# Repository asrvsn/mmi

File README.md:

# A stage-top micromanipulator/incubator 

This repository contains the specifications for a combined micromanipulator/incubator stage insert usable for cell/microorganism handling and immobilization for imaging, particularly during multi-day developmental dynamics.

It is fully open source, containing:
* 3D parts suitable for SLA printing: [insert](hardware/insert/parts), [frame](hardware/frame/parts), [capillary mounts](hardware/capillary_mounts/parts), [lid](hardware/lid/parts)
* PCB schematics and board layouts: [main](hardware/frame/main_pcb), [drive](hardware/frame/drive_pcb), [heating](hardware/lid/heating_pcb), [top plate](hardware/lid/plate_pcb)
* A complete [BOM](bom.xlsx)
* Software and firmware for operation: [app](app), [client](client), [firmware](firmware)
* [Assembly](#3d-printing--assembly) and [operating](#usage-and-operation) instructions

The 3D model and an assembled prototype, side by side:

Features of the insert are:
* A temperature (via Peltier) and flicker-free light-controlled enclosure fitting standard well-plates
* Motorized fine-motion XYZ axes (consisting of optical translation stages) for handling, cutting, and more general actuation of specimens via glass capillaries, jogged at commanded speeds down to ~10 um/s (open loop; the slow end is not yet characterised on the unit). A larger-stroke additional X axis consisting of a more traditional stepper leadscrew enables traversal of the entire well-plate width, allowing for:
* Parallelized capture and imaging of N specimens in a statically held row of capillaries, allowing for better control of batch variations.
* A combined syringe/gravity-driven flow control on all capillaries, allowing for transition between traditional displacement (syringe)-driven actuation suitable for capture and gentler pressure-driven immobilization suitable for imaging during development. The latter method is far more robust for multi-day holds and less perturbative during growth and development, where plastic deformations occur.
* Insert geometry fits into existing standard Zeiss "K" frame-style (110x160mm) stage openings as well as larger (130x160mm).
* Insert geometry and mass also enables stacking atop Z-actuated piezo inserts for rapid Z-stack acquisition. This is made possible by the ~1kg total mass of the insert, within typical 1.5-2kg Z-piezo load limits, and a second 130x160mm catch for the piezo stage's larger opening.
* As an insert, micromanipulation occurs as in motions composed with that of the stages, unlike traditional table-top micromanipulators (e.g. those used in electrophysiology). This enables both more natural user operation during manual placement with visual feedback, and also enables multiple captured specimens to be easily imaged using automated sequences (e.g. in ZEN software) without the need for external sync / triggers.
* Precise temperature control is available via a top-mounted (lid) Peltier assembly. This configuration both keeps the full under surface transparent, allowing RL illumination and imaging of the entire well-plate, and prevents Rayleigh-Benard type instability (convection cells) by heating the top rather than the bottom liquid surface. A fast control loop sets the lid surface temperature via on-board NTC's, while a slower loop changes the lid setpoint using readouts of dual medium-immersed temperature probes. The top-mounted heating lid has an imaging slot which retains TL illumination and widefield imaging capability (though not generally at optimal Kohler configuration due to the thickness of the unit) as well as t-PMT. 
* Blue- and red-shifted illumination using tunable-white CCT LED strips.
* Construction from commercially available hardware and 3D printed parts, with no specialized in-house machining or fabrication facilities required.
* Finally: **being an insert, it is designed for rapid setup and teardown in shared-use microscope facilities.** This is a primary benefit over larger built / bespoke setups e.g. with table-mounted micromanipulators or shrouding incubators.

The primary use-case is in time-lapse confocal laser scanning microscopy (CLSM) during growth and development with accurate simulation of diurnal cycles. Many other uses are possible. The use of a z-piezo insert in combination with SNR boosted acquisition methods (e.g. Zeiss Airyscan) enables rapid acquisition of z-stacks, hence this unit is designed to be compatible with this workflow.

Design notes of the current version (v1; v2 coming soon):
* The micromanipulation capability is fully open-loop (with only limit endstops) relying on visual feedback through eyepieces or cameras. Thus automated return sequences are not currently possible. A goal of v2 is to add position feedback. This will be accomplished by using serial-bus servos in v2, also eliminating the separate motor-drive board entirely (left flap seen above moving with the drive unit) and further reducing mass.
* Flow control (syringe- and gravity-driven) are fully manual, supported beside the microscope using unspecified, laboratory-dependent equipment (e.g. via standard hardware attaching to optical breadboards). V2 will motorize both methods of flow control, enabling integration with the other computer-controlled parts (actuation, lighting, and temperature), enabling some degree of experiment automation. Simultaneously, mounting hardware for the off-scope syringe assemblies will be included and further facilitate rapid setup / teardown.
* SLA printing is currently required due to fine details in the design. V2 will transition to an FDM-friendly design, in which parts can be more dimensionally stable depending on the material.
* In v2, the z-height of the unit will be reduced, enabling more optimal microscope condenser placement for widefield acquisition. 
* **Further firmware updates coming soon.**
<!-- * Firmware status: the drive (jogging, limit switches, halts), the lights and the lid run by hand: light levels and lid duty are set from the app's calibration pages or the protocol's `light` and `lid` commands. The lid's temperature control (the cascade above) and incubator programs (diurnal cycles on the Teensy's clock) are specified in [`firmware/api.md`](firmware/api.md) (9.3) and [`firmware/hardware.md`](firmware/hardware.md), but not yet implemented. -->

The complete Fusion 360 file of the assembly is [here](mmi.f3d).

# BOM

The complete bill of materials, including:
* non-3D printed hardware and adhesives
* stepper and servo motors
* experimental apparati
* through-hole / hand-soldered PCB components 

are in [`bom.xlsx`](bom.xlsx). These sheets organize by supplier and contain helper columns to track order status.

# Control system

Three PCBs make up the v1 control system: 
1. A [main board](hardware/frame/main_pcb) built around a Teensy 4.1 (left)
2. An aluminum-core, Peltier-heated [lid board](hardware/lid/heating_pcb) (center) and a [top-plate pcb](hardware/lid/plate_pcb) acting as a passive radiator.
3. A [motor drive board](hardware/frame/drive_pcb) (top) which moves along with the stepper rail and connects via flexible ribbon cable to the main board.

Send all four off to a PCB assembly service; here we include the assets for JLCPCB in each folder, with the order options in its `jlc/ORDER.md`. Order with those options, not the form's defaults: the heating board and the top plate are aluminium-base boards (ordered as default FR-4 they won't spread the heat), the main and drive boards are 4-layer ENIG with epoxy-filled vias, and the main board is assembled on its bottom side. Upon delivery, hand-soldering of several larger components is necessary, detailed in:
<!-- Follow these guides, which also hold each board's checks before first power (on a current-limited bench supply) and the order in which it meets the mechanical build below: -->

* [Main board](hardware/frame/main_pcb/assembly.md)
* [Lid (heating) board](hardware/lid/heating_pcb/assembly.md)
* [Drive board](hardware/frame/drive_pcb/assembly.md)

# Hardware (3D prints)

# 3D printing & assembly

In the following, we give 3D printing and assembly steps in brief. Detailed print settings are in [hardware/print.md](hardware/print.md).

## Stage insert

Print the [insert file](hardware/insert/parts/insert.step).

Epoxy the 8mm 440C balls to their pockets in `insert` to create a kinematic coupling.

## Unit frame

Print the [unit frame's parts](hardware/frame/parts): one of each, except three each of the two gears and the main enclosure's switch cap ([print.md](hardware/print.md)).

Epoxy magnets and dowels to the underside of `frame` to complete the kinematic coupling: one 8 x 3 mm magnet per pocket, then its dowel pair.

Epoxy balls topside (six: the capillary mount's and lid's couplings). Take the NEMA11 150mm actuator apart: keep the motor with its leadscrew, the carriage on its MGN9 rail, and the leadscrew's end bearing (in the kit's aluminium back plate); the kit's own frame and both aluminium plates aren't used. Press the end bearing into the frame's Ø13.15 seat at the bearing end, flush with the end face. Lay the rail in the frame's groove and bolt it through its 3rd, 5th and 7th holes with 3 x M3x12 socket heads into M3 nuts inset in the frame, tightened in turns to ~0.5 N·m (the nuts sit in resin).

Bolt the motor (3 x M2.5x8 button heads + washers, from inside the frame), snug only, threading the leadscrew through the carriage's nut into the end bearing (any stepper tester spins it quickly; or turn the shaft by hand). Run the carriage to the motor end, so the nut pulls the motor onto the screw's line on its pilot, then tighten the three screws in turns. Test full travel: the effort should stay even. If it tightens toward the motor end, repeat that alignment; toward the bearing end, open the Ø13.15 seat slightly on the side the screw pushes toward and fix the bearing with a drop of epoxy. Finish with a thin film of grease on the screw. Strong print warping or dimensional inaccuracies can make this unavoidable, in which case one option is to not place the end bearing, allowing the screw to move loosely.

Epoxy the 30T gear to the translator knob and bolt the 16T gear to the servo spline (M2.5x8 button head), x3. Translators are compact manual linear stages with a knob drive (not a micrometer head); servos are micro digital servos with a bottom wire exit, used as plain gearmotors. At this step, therefore, remove the servos' control boards (and positioning potentiometers), solder a twisted pair of 26 AWG silicone (~200 mm) to each motor's terminals and bring it out through the same exit ([drive board guide](hardware/frame/drive_pcb/assembly.md), step 8).

Bolt `y_brace` to the Y stage base: 2 x M2x6 button heads through the base into M2 nuts inset in the brace. The table covers the holes, so run the translator back and forth (turn the knob) to reach each of the two inset M2s in turn.

From the top, 2 x M4x8 countersunk through the brace into the base. Epoxy the brace's half of the wrist coupling: a pair of 6 x 2 mm magnets per pocket, then its dowel pair.

Fit the subminiature hinge-lever microswitches (8 per unit, low operating force) to the three printed faces and wire each stage-end pair NC in series with 30 AWG wire (the arm's channel has no room for 26 AWG on all sixteen switch wires): a bridge between the NC pins, a lead from each outer pin. `x_face` takes X's pair and the rail MAX switch (J8, the bearing end), `x_brace` Z's pair, `z_brace` Y's pair and the rail MIN switch (J7, the motor end). Every switch is wired COM to NC, its NO pin cut short ([drive board guide](hardware/frame/drive_pcb/assembly.md), step 9).

Slide the Y servo into `z_brace` (tabs on the wall; 2 x M2x16 into nuts in the side slots), then bolt `z_brace` to the Y table from below: 3 x M4x10 and 2 x M2x10 countersunk.

Bolt the Z stage base to `z_brace` as for Y: 2 x M2x6 button heads into inset M2 nuts, the stage driven to its top end to reach the hole.

Z servo into `x_brace` (2 x M2x16 + nuts), then `x_brace` onto the Z table: 3 x M4x10, 2 x M2x10 countersunk.

X stage base onto `x_brace`: 2 x M2x6 button heads into inset M2 nuts.

X servo into `x_face`, body first (2 x M2x16 + nuts). Bolt the drive board's arm to `x_face`: 2 x M2x20 into nuts recessed in the arm.

`x_face` onto the X table: 3 x M4x10, 3 x M2x10 countersunk, heads on the face.

Drive board, wires first and covers last ([drive board guide](hardware/frame/drive_pcb/assembly.md), steps 3-15):
1. The ribbon: measure the 20-way IDC ribbon (2.54 mm pitch, sockets on both ends) in place (the guide's step 3 dry-fits the tray, the main board and `x_face` for it), as a U-loop from the main board's J1 that rolls with the carriage, and cut the far socket off where it meets J2's pads (~250-300 mm). Solder that end to the J2 pads, red stripe on pad 1, and buzz it (H1) before any switch is wired. Strain relief: a bead of neutral-cure RTV or epoxy across the ribbon (no room for a cable tie).
2. The board into the arm's frame. Per axis, route the servo's motor pair and the switch pair along the arm's channel, cut them to length and solder them: motors to J4-J6, the stop chains to J9/J11/J13, the rail's MIN and MAX switches to J7 and J8. Check them at the IDC socket (H3).
3. Then the housing: back plate + front cover, 4 x M2x10 + nuts.

Slide the rail carriage into `x_face` from the side as shown (its lip hugs the carriage) and bolt the plate to it: 4 x M3x10 countersunk from the top.

Cut two 100 mm lengths of tunable-white 24 V LED strip (COB; cut only at its 50 mm marks, and the walls take up to 120 mm) and stick them on edge to the frame's long inner walls, LEDs facing the plate. Link the strips' 24V, W- and C- pads at the bearing end, and run three leads from the motor end through the frame's lead tunnel to a 3-pin PH plug for the main board's J16 (halved pre-crimped leads: pin 1 24V, pin 2 W- (warm), pin 3 C- (cool); [main board guide](hardware/frame/main_pcb/assembly.md), step 19).

Bolt the main enclosure's tray to the frame's three end pads: 3 x M3x8 countersunk from the frame side into M3 nuts in the tray's bosses.

Main board, hand-assembled and checked through M8 of [its guide](hardware/frame/main_pcb/assembly.md) (Teensy 4.1 in its sockets), into the tray: plug in the rail motor (J3) and the LED strip (J16), the unit off. The rail motor's lead ends in bare wires: make its 4-pin ZH plug as in the guide's step 18 (pin 1 black, 2 green, 3 red, 4 blue), and never plug or unplug it live. Cover on with 3 x M2x20 socket heads into M2 nuts in the tray's back face; switch caps in from the top. The ribbon's IDC socket mates on J1 through the cover's opening.

<!-- The unit's first power-up, everything plugged in, is the main board guide's S1-S3: on the current-limited bench supply first, then the 24 V supply. -->

## Capillary mounts

Print the [capillary mount files](hardware/capillary_mounts/parts).

Epoxy the mount's half of its coupling to its underside: a pair of 8 x 3 mm magnets per pocket, then its dowel pair; glue in the three M2 nuts for the face plate. On `end_effector_base`, epoxy its three Ø6 mm balls (440C or chrome steel: they sit on magnets) and press in the two M2 nuts for the clamp cover from below.

Press 2 mm solid silicone cord (~0.22 m per unit) into the clamping plates' grooves, cut flush: four lengths in `face_plate`, two in `end_effector_clamp`. If using the 3 mm foam cord instead, check the cord parameters in Fusion before printing the plates.

## Peltier-heated lid

Print the [lid frame](hardware/lid/parts/lid_frame.step).

Epoxy the lid frame's half of its coupling: one 8 x 3 mm magnet per pocket, then its dowel pair.

The heating board follows [its guide](hardware/lid/heating_pcb/assembly.md). All its hot-plate work comes before the frame, whose resin softens from ~77 °C:
1. In one hot-plate session (~100 °C):
   * the six 20 x 20 mm Peltier modules on thermal paste, their leads soldered to PE1-PE6;
   * the two medium probes (10k NTC in a Ø3 x 12 mm stainless cap, AWG28 PTFE leads) on J2 and J3, either lead on either pad. Cut the leads to ~55 mm (J2) and ~115 mm (J3) from the cap (46-48 and 107-109 mm in the model, plus leeway), strip ~2 mm and tin;
   * the 7 x 26 AWG lid cable on J1 (twisted in pairs: +24 V/GND, SDA/SCL, IN1/IN2, plus a second GND).
2. Thread the cable through `lid_frame`'s +X tower channel (the frame hangs on it until glued), make its 7-pin PH plug for the main board's J20 (wire n to pin n), and run the board's checks on the main board.
3. Paint the aluminium (chamber) side matt black, put a 7 mm piece of polyimide tape over MH1, MH2, MH4 and MH6, then epoxy the board into `lid_frame`.
4. Conformal coat the copper side with TCO1 (the Peltier string's thermal cutoff) masked, as the coat can glue its contacts shut; mask the Peltier tops and the six screw holes too.
5. Dress the probe leads: each pair runs from its pads over the imaging slot's edge, down through the slot and along the board's underside, then down to its cap, which lies flat on the dish floor just past the coverslips' outer end, tip away from you: J2's through the slot's -X end, J3's between R16 and PE2 to the slot's +Y edge, then under the board to the +X end.

Top plate on thermal paste over the six Peltiers, 6 x M3x10 button heads from below into M3 nuts on top: tighten evenly, the Peltiers sandwiched tight between board and plate. Then line the slot with polyimide tape, bridging the gap between board and plate, and run a bead of neutral-cure silicone into the tower's channel round the cable (guide steps 15-16).

## Completed unit

# Software

The Teensy 4.1's firmware, a Python client library with a test server that stands in for the unit, and the operator's app.

| | |
|---|---|
| `firmware/` | the firmware (`stage/`), its protocol (`api.md`), parameters, hardware rules and host tests: `firmware/README.md` |
| `client/` | `mmi_client`: the client library (standard library only) and the test server: `client/README.md` |
| `app/` | `mmi_app`: the operator's window, driven by a hand controller or the keyboard: `app/README.md` |
| `env.yml` | the `mmi` conda env: both packages and all they need |
| `start_application` | starts the app, on the unit or a test server (a Mac or Linux) |
| `write_firmware` | builds the firmware, writes it to the Teensy over USB, and checks it (a Mac or Linux) |

## Install

With conda (Miniforge), from this folder:

```sh
conda env create -f env.yml     # once: Python 3.12, PyQt6, pyqtgraph, pygame ..., and client/ + app/ installed editable
conda activate mmi              # for the test server and the tests (start_application finds the env itself)
conda env update -f env.yml     # after env.yml changes
```

Any other Python 3.11+: `pip install -e client -e app` (their `pyproject.toml` list what they need;
`pip install -e "client[test]" -e "app[test]"` adds pytest). The tests: `pytest` in `client/` and in `app/`
(offscreen); the firmware's, `firmware/test/run.sh`.

## Write the firmware

The first flash is part of the main board's bring-up (its guide, step T). For updates: with Teensy USB exposed without enclosure and all board switches off, connect micro-usb to controller PC and execute `./write_firmware`. It builds, uploads, and checks
the `!hello` (`firmware/README.md`, "Building and flashing"). Then, close the enclosure; do not connect to USB during normal operation with 24v plugged in.

## Start the app

```sh
./start_application                  # the unit, over wired Ethernet
./start_application 127.0.0.1        # the test server on this computer (below)
```

- **The unit:** the cable from this computer's Ethernet port or adapter into the unit's J19, the unit on (PWR, SW9). It
waits for the link, gives the interface 192.168.50.1/24 if it hasn't an address there (your password; temporary),
waits for the unit, says which gamepad the app will take, and starts the app.
- **Any other address** skips the Ethernet set-up and waits until something answers there.
- **The app's own arguments** pass through: `--fullscreen`, `-v` (log connects, drops and inputs), `--config my.toml`
(`app/config.example.toml`). It won't start a second app while one is open.
- **Driving:** MOTORS (SW11) on, then the sticks and triggers, and MOTORS off again when done; B (Circle, Space) halts; HOME (PS, Esc) opens the menu:
`app/README.md`, "Controls".

## Test with the test server

```sh
python -m mmi_client.test_server     # shell 1, in the mmi env: the unit on 127.0.0.1:5000, printing what it's sent
./start_application 127.0.0.1        # shell 2: the app, driving it
```

- **It simulates the unit at the protocol level:** the drive with its lease and halt, the stage's travel and its limit
switches, stalls, MOTORS, the lights and the lid (with its thermal model). Options: `--motors-off`, `--strict`,
`0.0.0.0:5000` to be reachable from another machine (the Pi): `client/README.md`.
- **With Fusion 360:** start Fusion with its MCP add-in (it listens on 127.0.0.1:27182) and open the `mmi` design,
with its "kin: rail / X / Z / Y" joints. The test server finds it by itself and drives those joints, so every jog
moves the model on screen, stopping at the stage's ends; Ctrl-C puts them back to the as-built pose. Without Fusion
it simply runs; `--no-fusion` keeps it out even with Fusion open.

# Experiment preparation

Fluids preparation for an experiment.

## Syringe assembly

Fill the syringe (2.5 mL gastight glass) fully and purge it tip up, to a droplet at the Luer tip. Assemble: the reservoir line's (1/16" ID) female fitting on the stopcock's (3-way female x female x male, locking Luer) male port, the outlet's male fitting in its in-line female port, the syringe into the side port, OFF toward the outlet. The Luer tip is a slip fit, so seat it firmly.

OFF right (toward the reservoir line); push 1 cm to fill the outlet to a droplet.

OFF left; push 1 cm to fill the reservoir line to a droplet at its end.

Line into the reservoir flask (T25 culture flask used as reservoir), its end 1 cm off the floor; pull the plunger fully out to refill. Repeat per syringe assembly.

## Capillaries

We generally use 2.00 mm OD x 1.00 mm ID borosilicate capillaries. Leave blunt for **dispensing** lines, pull to desired ID for **capture** and **actuation** lines. Follow standard procedures for pulling larger (50-100um) tips as needed, e.g. pulling smaller and then scoring and breaking against ceramic tile. A starting point on a Sutter P-97 with a box filament (from the Sutter Pipette Cookbook's large-tip programs, untested on this glass): run a ramp test, then HEAT = ramp + 25, PULL 0, VEL 140, TIME 100, pressure 200; 2 mm glass should pull 15-25 s after pressing PULL (adjust HEAT in steps of 5). The ID/OD ratio stays about 0.5, so for a 100 um ID tip, score where the OD is about 200 um.

OFF right. Push 10 cm of tubing onto the outlet barb and a blunt (unpulled) capillary 3 mm into its end; push 1 cm to fill to a droplet. Repeat per dispensing capillary.

Dip the dispensor's tip in the sample (e.g. a 60 mm dish) and pull 2 cm back to draw it up the capillary and into the tube.

As for the dispensors, with pulled capture capillaries, tips broken back to ~50 um ID. Repeat per capture capillary.

The same for the two shorter actuator capillaries.

Lay the actuator capillaries in the end effector's grooves and caliper each tip to 20.3 mm beyond the base's end face (the nominal pose, open loop). Clamp cover on: 2 x M2x8 countersunk hex. Keep the capillary tips upright throughout, so no air gets in.

Lay the capillaries on the mount's ramp, the dispensors innermost in each group (8th and 9th): captures to 42.4 mm beyond the mount's end face, dispensors to 39.6 mm. Face plate on: 3 x M2x8. Keep the capillary tips upright throughout, so no air gets in.

## Well plate

Cut two 44 x 16 mm windows in the single-well plate's floor (a rotary tool) for 22 x 50 mm (No. 1.5) coverslips: centred across the plate's width, either side of a 7 mm rib on its centre line, 16.4-60.4 and 67.4-111.4 mm along its length from either outer end. Each coverslip overlaps its window by 3 mm all round, and the row's capillary tips sit over them. File the edges, and clean all surfaces with IPA. Glue the coverslips on using a UV-cured optical adhesive rated USP Class VI, e.g. NOA 81. Rinse with clean solvent (e.g. DI water) and test for leaks. Ensure the coverslips mount from the bottom, as this ensures objectives don't snag on well plate surfaces.

## On the microscope

Insert into microscope's stage insert (standard "K" frame or larger z-piezo openings both supported); well plate in, with ~5 mm of medium (~49 mL).

Lower the frame onto the insert's kinematic coupling.

Snap the end effector onto its wrist coupling and press its two tubes into `x_face`'s clips: the lip clip, then up the vertical clips. Their line runs to the actuators' syringe assembly beside the scope.

Snap the capillary mount onto its coupling; its tubes run to the dispensors' and captures' syringe assemblies.

Lid onto its coupling; its cable into the main board's J20.

Lower the condenser; microscope is ready to image.

# Run experiment

The unit takes 24 V DC, centre positive, into J15 (a 5.5 x 2.1 mm plug), from a supply set to 24.0 V with its trimmer locked; never above, as the boards' surge-protection diodes conduct from 26.7 V. The [main board guide](hardware/frame/main_pcb/assembly.md) ("The 24 V supply") covers the supply's mains wiring and its -V to earth link. Connect Ethernet (J19) to the PC running the application specified above.

The three switches run front to back from the operator and switch on toward the back: PWR (SW9) the unit, MOTORS (SW11) the rail and the fine axes, LID HEAT (SW10) the lid's heater. Switch on PWR, then MOTORS while positioning, then LID HEAT. Once the organisms are placed, switch MOTORS off again: leave it off for incubation and whenever nobody is at the unit (unpowered, nothing can move, stall or heat). Upon shutdown, flip the switches in reverse order and disconnect power and Ethernet. Consult [operation/README.md](operation/README.md) for the detailed rules of operation, including moves the limit switches don't guard against.

Many configurations are possible. Here we show one where the left actuator serves as a pick-and-place effector, while the right carries a sharper tip for cutting, injection, or microsurgery. On the static side, we show two different dispensing lines, perhaps with different strains or cell lines. Visual feedback confirms pick and place from respective dispensing lines. Other lines are imaging mounts, in which organisms or cells are held either by syringe action (classical) or by gravity-driven hydrostatic pressure difference (typically resulting in a much smaller force, still stable for multi-day imaging and suitable for plastic deformations occuring during growth and development). 

Any configuration of the capillaries as mounts, actuators, or tools is in principle possible; the static capillary row serves as a "Turing tape" of sorts. V2 will support mid-experiment control using direct acquisition PC commands e.g. as Experiment Designer blocks in ZEN.

# Cleanup & preparation for next use

After use, all surfaces contacting fluid bodies (highlighted in blue), should be cleaned or disposed of. These include the inlet and outlet lines and well plate bath and flask reservoirs. The contacting surfaces of `mmi` to these bodies is minimized to a few non-disposable components.

The immersed temperature probes and glass syringes, highlighted in red, require cleaning and/or disinfection e.g. with 70% ethanol. The syringes can be autoclaved, but not the probes.

All other materials can be disposed of and replaced sterile between uses: culture flasks, tubing, stopcocks, Luer barbs, capillaries, and well plate-cover slip assembly.

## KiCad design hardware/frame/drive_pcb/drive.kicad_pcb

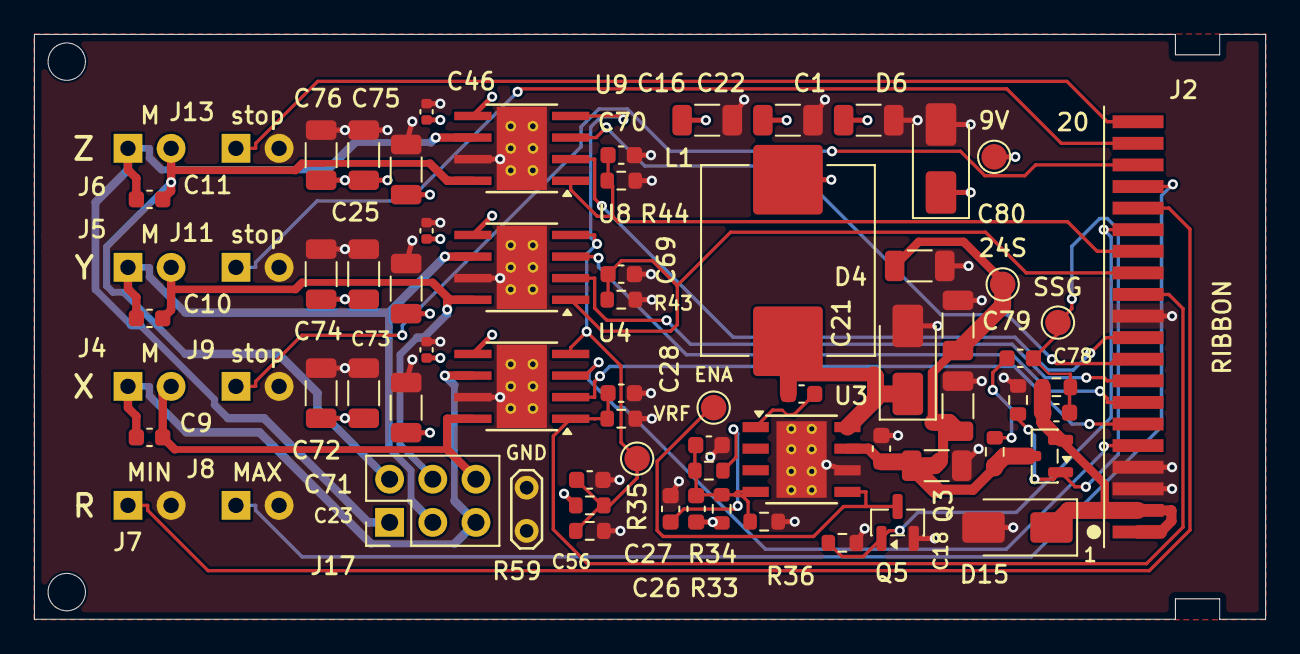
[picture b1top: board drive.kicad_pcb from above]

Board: 4 copper layers, 72.4 x 34.4 mm, 73 parts (0 on the bottom side), 33 nets.

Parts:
C1, C16, C22, C23, C24, C25, C71, C72, C73, C74, C75, C76: 22u 25V; C_1206_3216Metric
C9, C10, C11, C21, C68, C69, C70, C78: 10n 50V; C_0603_1608Metric
C18, C53, C79, C80: 10u 50V; C_1206_3216Metric
C19: 100n 50V; C_0603_1608Metric
C26: 2n2 50V; C_0603_1608Metric
C27: 68n 50V; C_0603_1608Metric
C28: 100p 50V; C_0603_1608Metric
C44, C45, C46: 100n 50V; C_0402_1005Metric
C56: 100n; C_0603_1608Metric
C77: 1u 50V; C_0603_1608Metric
D4: SS34; D_SMA
D6: SMAJ12A; D_SMA
D15: SMAJ24A; D_SMA
J2: Ribbon pads (20 x 1.27 mm); SolderPads_1x20_P1.27mm_Ribbon_Pad1Bottom
J4: X motor; WireHoles_1x02_P2.54mm_D0.9mm
J5: Y motor; WireHoles_1x02_P2.54mm_D0.9mm
J6: Z motor; WireHoles_1x02_P2.54mm_D0.9mm
J7: rail MIN (home); WireHoles_1x02_P2.54mm_D0.9mm
J8: rail MAX; WireHoles_1x02_P2.54mm_D0.9mm
J9: X stops; WireHoles_1x02_P2.54mm_D0.9mm
J11: Y stops; WireHoles_1x02_P2.54mm_D0.9mm
J13: Z stops; WireHoles_1x02_P2.54mm_D0.9mm
J17: Motors (test); PinHeader_2x03_P2.54mm_Vertical
L1: 22u 4.4A; L_Sunlord_MWSA1004S
MH1, MH2: M2; MountingHole_2.2mm_M2
Q3: HL2309; SOT-23
Q5: 2N7002; SOT-23
R33: 13k; R_0603_1608Metric
R34, R42, R43, R44: 2k; R_0603_1608Metric
R35: 820; R_0603_1608Metric
R36, R78: 100k; R_0603_1608Metric
R58: 10k; R_0603_1608Metric
R59: 4k7; R_0603_1608Metric
R79: 150k; R_0603_1608Metric
R80: 1k; R_0603_1608Metric
TP11: 24S; TestPoint_Pad_D1.5mm
TP12: SSG; TestPoint_Pad_D1.5mm
TP13: 9V; TestPoint_Pad_D1.5mm
TP14: VRF; TestPoint_Pad_D1.5mm
TP15: ENA; TestPoint_Pad_D1.5mm
TP16: GND; TestPoint_2Pads_Pitch2.54mm_Drill0.8mm
U3: TPS5430DDA; TI_SO-PowerPAD-8_ThermalVias
U4, U8, U9: DRV8251ADDA; Texas_HTSOP-8-1EP_3.9x4.9mm_P1.27mm_EP2.95x4.9mm_Mask2.4x3.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

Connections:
+9V: C1.1, C16.1, C22.1, C23.1, C24.1, C25.1, C26.1, C44.1, C45.1, C46.1, C71.1, C72.1, C73.1, C74.1, C75.1, C76.1, D6.1, L1.2, R33.1, R58.1, TP13.1, U4.5, U8.5, U9.5
/BOOT9: C21.2, U3.1
/ENA9: Q5.3, TP15.1, U3.5
/FB9: C26.2, C28.1, R33.2, R34.1, R35.1, U3.4
/HEAD_24V: C77.1, D15.1, J2.1, J2.2, Q3.2, R78.1
/HEAD_24V_SS: C18.1, C19.1, C53.1, C79.1, C80.1, Q3.3, R80.1, TP11.1, U3.7
/MX_A: C9.1, J4.1, J17.5, U4.6
/MX_B: C9.2, J4.2, J17.6, U4.8
/MX_IN1_C: J2.5, U4.3
/MX_IN2_C: J2.6, U4.2
/MX_IP: C68.1, J2.12, R42.1, U4.1
/MY_A: C10.1, J5.1, J17.3, U8.6
/MY_B: C10.2, J5.2, J17.4, U8.8
/MY_IN1_C: J2.7, U8.3
/MY_IN2_C: J2.8, U8.2
/MY_IP: C69.1, J2.13, R43.1, U8.1
/MZ_A: C11.1, J6.1, J17.1, U9.6
/MZ_B: C11.2, J6.2, J17.2, U9.8
/MZ_IN1_C: J2.9, U9.3
/MZ_IN2_C: J2.10, U9.2
/MZ_IP: C70.1, J2.14, R44.1, U9.1
/PH_9V: C21.1, D4.1, L1.1, U3.8
/SS_G: C77.2, C78.2, Q3.1, R78.2, R79.1, TP12.1
/SS_M: C78.1, R80.2
/SW_MAX: J2.17, J8.1
/SW_MIN: J2.16, J7.1
/SW_X: J2.18, J9.1
/SW_Y: J2.19, J11.1
/SW_Z: J2.20, J13.1
/V9_OFF_C: J2.15, Q5.1, R36.1
/VREF_H: C56.1, R58.2, R59.1, TP14.1, U4.4, U8.4, U9.4
/ZC9: C27.1, R35.2
GND: C1.2, C16.2, C18.2, C19.2, C22.2, C23.2, C24.2, C25.2, C27.2, C28.2, C44.2, C45.2, C46.2, C53.2, C56.2, C68.2, C69.2, C70.2, C71.2, C72.2, C73.2, C74.2, C75.2, C76.2, C79.2, C80.2, D4.2, D6.2, D15.2, J2.3, J2.4, J2.11, J7.2, J8.2, J9.2, J11.2, J13.2, Q5.2, R34.2, R36.2, R42.2, R43.2, R44.2, R59.2, R79.2, TP16.1, TP16.2, U3.6, U3.9, U4.7, U4.9, U8.7, U8.9, U9.7, U9.9

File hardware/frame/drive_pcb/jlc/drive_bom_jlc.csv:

Comment,Designator,Footprint,LCSC Part #
22u 25V,"C1,C16,C22,C23,C24,C25,C71,C72,C73,C74,C75,C76",C_1206_3216Metric,C12891
10n 50V,"C9,C10,C11,C21,C78",C_0603_1608Metric,C57112
10u 50V,"C18,C53,C79,C80",C_1206_3216Metric,C13585
100n 50V / 100n,"C19,C56",C_0603_1608Metric,C14663
2n2 50V,C26,C_0603_1608Metric,C1604
68n 50V,C27,C_0603_1608Metric,C31658
100p 50V,C28,C_0603_1608Metric,C14858
100n 50V,"C44,C45,C46",C_0402_1005Metric,C307331
1u 50V,C77,C_0603_1608Metric,C15849
SS34,D4,D_SMA,C8678
SMAJ12A,D6,D_SMA,C19077531
SMAJ24A,D15,D_SMA,C19077541
22u 4.4A,L1,L_Sunlord_MWSA1004S,C408489
HL2309,Q3,SOT-23,C28646263
2N7002,Q5,SOT-23,C8545
13k,R33,R_0603_1608Metric,C22797
2k,"R34,R42,R43,R44",R_0603_1608Metric,C22975
820,R35,R_0603_1608Metric,C23253
100k,"R36,R78",R_0603_1608Metric,C25803
10k,R58,R_0603_1608Metric,C25804
4k7,R59,R_0603_1608Metric,C23162
150k,R79,R_0603_1608Metric,C22807
1k,R80,R_0603_1608Metric,C21190
TPS5430DDA,U3,TI_SO-PowerPAD-8_ThermalVias,C9864
DRV8251ADDA,"U4,U8,U9",Texas_HTSOP-8-1EP_3.9x4.9mm_P1.27mm_EP2.95x4.9mm_Mask2.4x3.1mm_ThermalVias,C5218844

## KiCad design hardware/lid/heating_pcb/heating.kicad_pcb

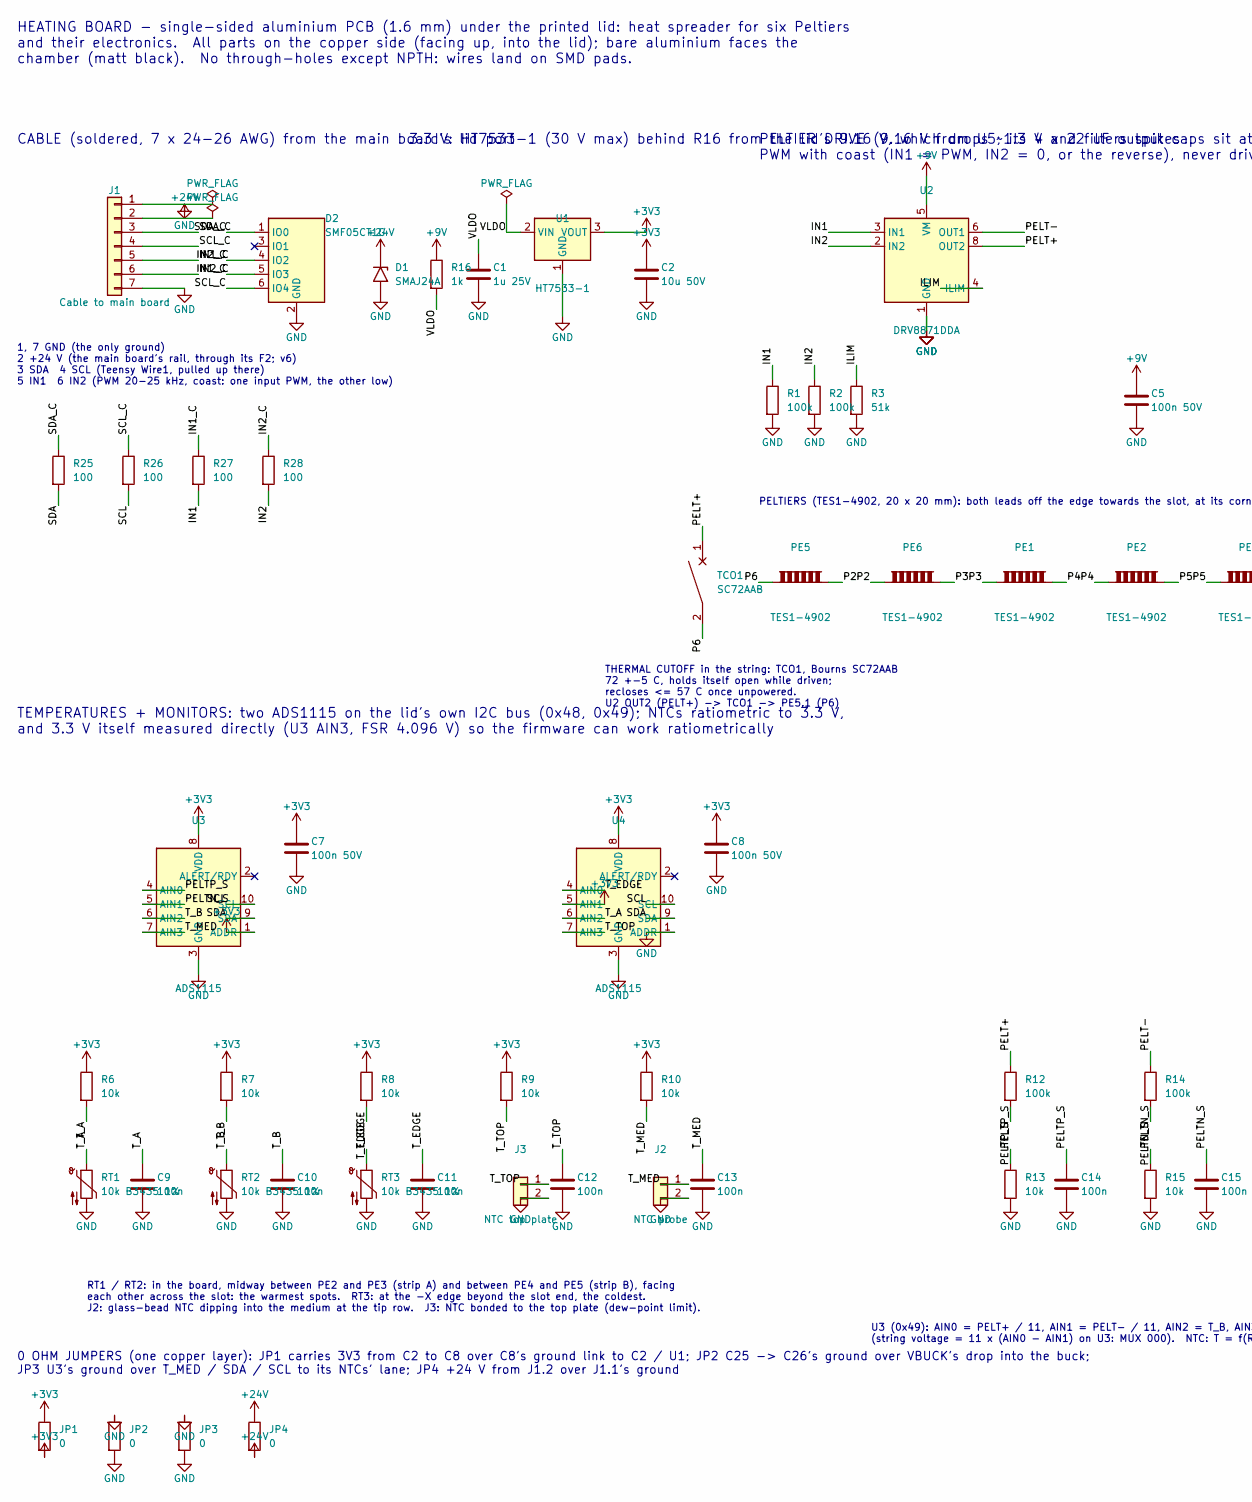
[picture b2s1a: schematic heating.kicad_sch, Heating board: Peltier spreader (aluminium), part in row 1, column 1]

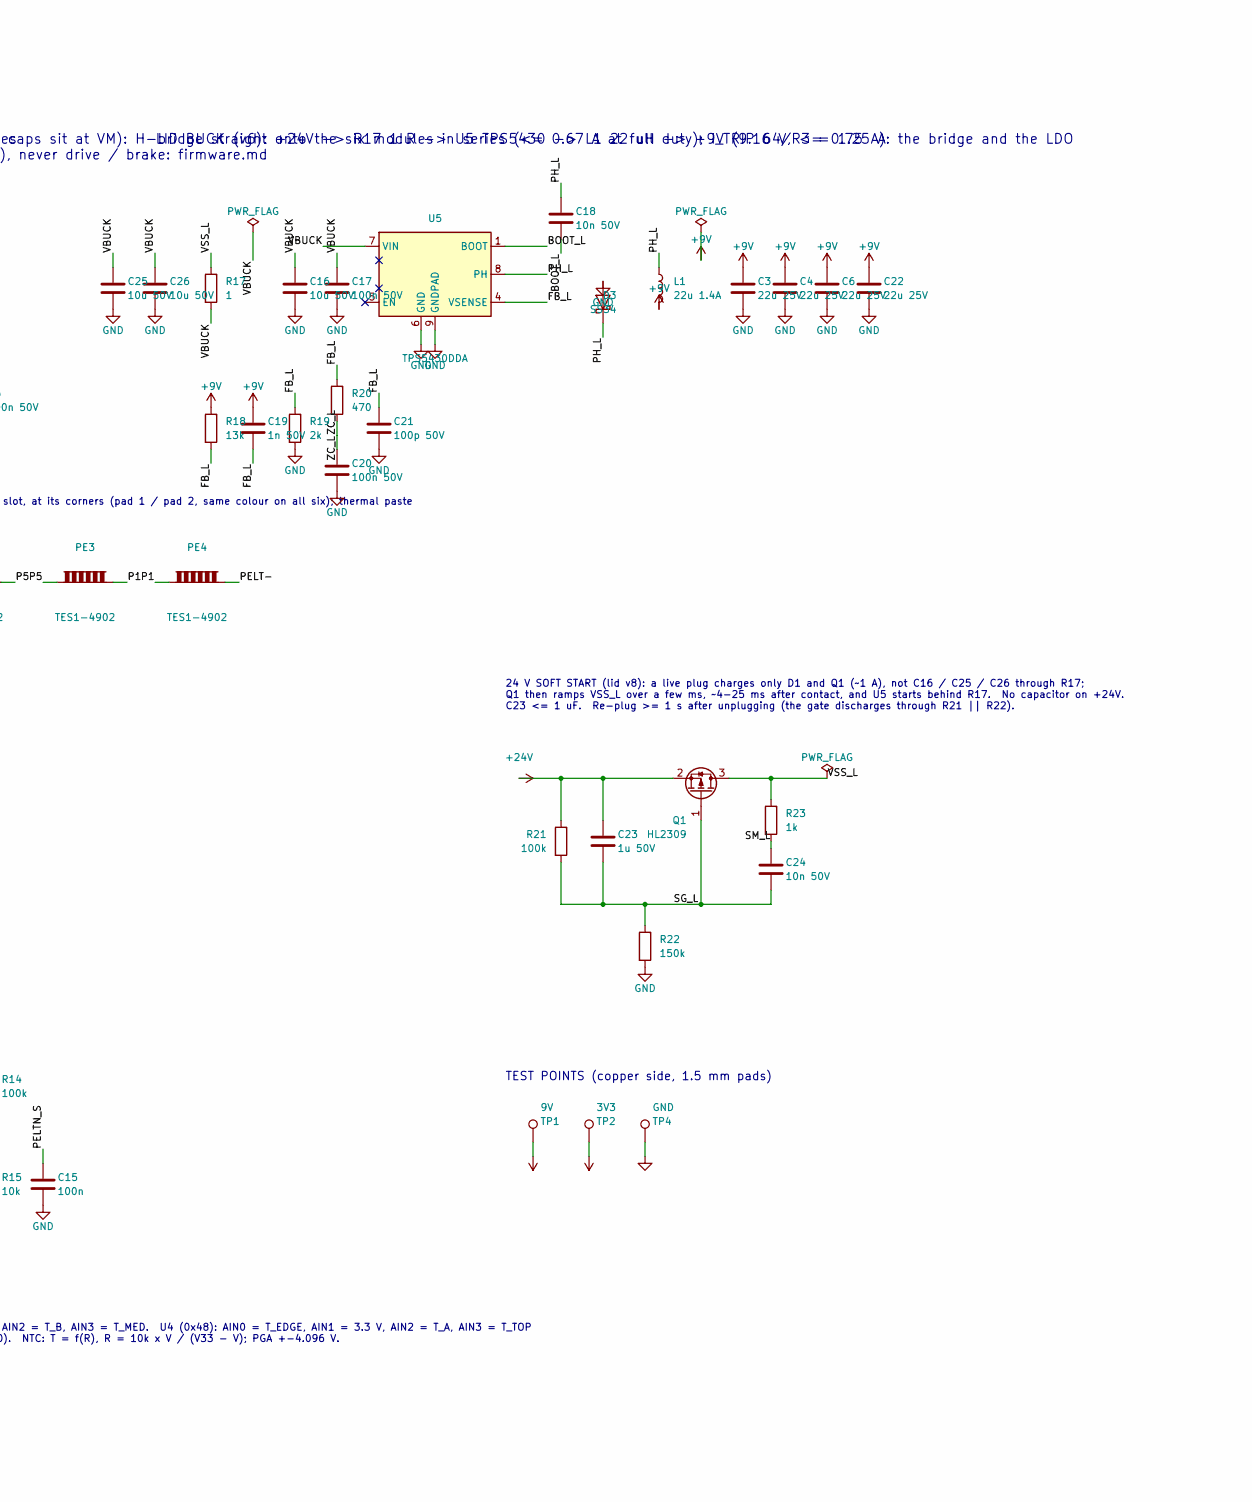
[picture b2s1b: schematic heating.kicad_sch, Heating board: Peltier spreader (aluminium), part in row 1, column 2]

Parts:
C1: 1u 25V; C_0402_1005Metric; LCSC C52923
C2, C16, C25, C26: 10u 50V; C_1206_3216Metric; LCSC C13585
C3, C4, C6, C22: 22u 25V; C_1206_3216Metric; LCSC C12891
C5, C17, C20: 100n 50V; C_0402_1005Metric; LCSC C307331
C7, C8: 100n 50V; C_1206_3216Metric; LCSC C24497
C9, C10, C11, C12, C13, C14, C15: 100n; C_0402_1005Metric; LCSC C1525
C18: 10n 50V; C_0402_1005Metric; LCSC C15195
C19: 1n 50V; C_0402_1005Metric; LCSC C1523
C21: 100p 50V; C_0402_1005Metric; LCSC C1546
C23: 1u 50V; C_0603_1608Metric; LCSC C15849
C24: 10n 50V; C_0603_1608Metric; LCSC C57112
D1: SMAJ24A; D_SMA; LCSC C19077541
D2: SMF05CT1G; SOT-363_SC-70-6; LCSC C15879
D3: SS34; D_SMA; LCSC C8678
J1: Cable to main board; SolderPads_1x07_P1.8mm_Narrow_Hand
J2: NTC probe; SolderPads_1x02_P2.0mm_Hand
J3: NTC top plate; SolderPads_1x02_P2.0mm_Hand
JP1: 0; R_0603_1608Metric_Jumper; LCSC C21189
JP2, JP3, JP4: 0; R_1206_3216Metric_Jumper; LCSC C17888
L1: 22u 1.4A; L_Sunlord_SWPA6028S; LCSC C51349
PE1, PE2, PE3, PE4, PE5, PE6: TES1-4902; Peltier_20x20_LeadsInner_Hand
Q1: HL2309; SOT-23; LCSC C28646263
R1, R2, R12, R14: 100k; R_0402_1005Metric; LCSC C25741
R3: 51k; R_0402_1005Metric; LCSC C25794
R6, R7, R8, R9, R10, R13, R15: 10k; R_0402_1005Metric; LCSC C25744
R16: 1k; R_1206_3216Metric; LCSC C4410
R17: 1; R_1206_3216Metric; LCSC C17928
R18: 13k; R_0603_1608Metric; LCSC C22797
R19: 2k; R_0402_1005Metric; LCSC C4109
R20: 470; R_0402_1005Metric; LCSC C25117
R21: 100k; R_0603_1608Metric; LCSC C25803
R22: 150k; R_0603_1608Metric; LCSC C22807
R23: 1k; R_0603_1608Metric; LCSC C21190
R25, R27, R28: 100; R_0603_1608Metric; LCSC C22775
R26: 100; R_1206_3216Metric; LCSC C17901
RT1, RT2, RT3: 10k B3435 1%; R_0603_1608Metric; LCSC C13564
TCO1: SC72AAB; Bourns_SC_TCO; LCSC C2859510
TP1: 9V; TestPoint_Pad_D1.5mm
TP2: 3V3; TestPoint_Pad_D1.5mm
TP4: GND; TestPoint_Pad_D1.5mm
U1: HT7533-1; SOT-89-3; LCSC C14289
U2: DRV8871DDA; Texas_HTSOP-8-1EP_3.9x4.9mm_P1.27mm_EP2.95x4.9mm_NoVias; LCSC C75864
U3, U4: ADS1115; TSSOP-10_3x3mm_P0.5mm; LCSC C37593
U5: TPS5430DDA; TI_SO-PowerPAD-8; LCSC C9864

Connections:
+3V3: C2.1, C7.1, C8.1, JP1.1, JP1.2, R6.1, R7.1, R8.1, R9.1, R10.1, TP2.1, U1.3 (VOUT), U3.1 (ADDR), U3.8 (VDD), U4.5 (AIN1), U4.8 (VDD)
+9V: C3.1, C4.1, C5.1, C6.1, C19.1, C22.1, L1.2, R16.1, R18.1, TP1.1, U2.5 (VM)
+24V: C23.1, D1.1 (A1), J1.2, JP4.1, JP4.2, Q1.2 (S), R21.1
/BOOT_L: C18.2, U5.1 (BOOT)
/FB_L: C19.2, C21.1, R18.2, R19.1, R20.1, U5.4 (VSENSE)
/ILIM: R3.1, U2.4 (ILIM)
/IN1: R1.1, R27.2, U2.3 (IN1)
/IN1_C: D2.5 (IO3), J1.5, R27.1
/IN2: R2.1, R28.2, U2.2 (IN2)
/IN2_C: D2.4 (IO2), J1.6, R28.1
/P1: PE3.2, PE4.1
/P2: PE5.2, PE6.1
/P3: PE1.1, PE6.2
/P4: PE1.2, PE2.1
/P5: PE2.2, PE3.1
/P6: PE5.1, TCO1.2
/PELT+: R12.1, TCO1.1, U2.8 (OUT2)
/PELT-: PE4.2, R14.1, U2.6 (OUT1)
/PELTN_S: C15.1, R14.2, R15.1, U3.5 (AIN1)
/PELTP_S: C14.1, R12.2, R13.1, U3.4 (AIN0)
/PH_L: C18.1, D3.1 (K), L1.1, U5.8 (PH)
/SCL: R26.2, U3.10 (SCL), U4.10 (SCL)
/SCL_C: D2.6 (IO4), J1.4, R26.1
/SDA: R25.2, U3.9 (SDA), U4.9 (SDA)
/SDA_C: D2.1 (IO0), J1.3, R25.1
/SG_L: C23.2, C24.2, Q1.1 (G), R21.2, R22.1
/SM_L: C24.1, R23.2
/T_A: C9.1, R6.2, RT1.1, U4.6 (AIN2)
/T_B: C10.1, R7.2, RT2.1, U3.6 (AIN2)
/T_EDGE: C11.1, R8.2, RT3.1, U4.4 (AIN0)
/T_MED: C13.1, J2.1, R10.2, U3.7 (AIN3)
/T_TOP: C12.1, J3.1, R9.2, U4.7 (AIN3)
/VBUCK: C16.1, C17.1, C25.1, C26.1, R17.2, U5.7 (VIN)
/VLDO: C1.1, R16.2, U1.2 (VIN)
/VSS_L: Q1.3 (D), R17.1, R23.1
/ZC_L: C20.1, R20.2
GND: C1.2, C2.2, C3.2, C4.2, C5.2, C6.2, C7.2, C8.2, C9.2, C10.2, C11.2, C12.2, C13.2, C14.2, C15.2, C16.2, C17.2, C20.2, C21.2, C22.2, C25.2, C26.2, D1.2 (A2), D2.2 (GND), D3.2 (A), J1.1, J1.7, J2.2, J3.2, JP2.1, JP2.2, JP3.1, JP3.2, R1.2, R2.2, R3.2, R13.2, R15.2, R19.2, R22.2, RT1.2, RT2.2, RT3.2, TP4.1, U1.1 (GND), U2.1 (GND), U2.7 (GND), U2.9 (GND), U3.3 (GND), U4.1 (ADDR), U4.3 (GND), U5.6 (GND), U5.9 (GNDPAD)

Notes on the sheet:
HEATING BOARD - single-sided aluminium PCB (1.6 mm) under the printed lid: heat spreader for six Peltiers and their electronics. All parts on the copper side (facing up, into the lid); bare aluminium faces the chamber (matt black). No through-holes except NPTH: wires land on SMD pads.
THERMAL CUTOFF in the string: TCO1, Bourns SC72AAB 72 +-5 C, holds itself open while driven; recloses <= 57 C once unpowered. U2 OUT2 (PELT+) -> TCO1 -> PE5.1 (P6)
24 V SOFT START (lid v8): a live plug charges only D1 and Q1 (~1 A), not C16 / C25 / C26 through R17; Q1 then ramps VSS_L over a few ms, ~4-25 ms after contact, and U5 starts behind R17. No capacitor on +24V. C23 <= 1 uF. Re-plug >= 1 s after unplugging (the gate discharges through R21 || R22).
1, 7 GND (the only ground) 2 +24 V (the main board's rail, through its F2; v6) 3 SDA 4 SCL (Teensy Wire1, pulled up there) 5 IN1 6 IN2 (PWM 20-25 kHz, coast: one input PWM, the other low)
TEMPERATURES + MONITORS: two ADS1115 on the lid's own I2C bus (0x48, 0x49); NTCs ratiometric to 3.3 V, and 3.3 V itself measured directly (U3 AIN3, FSR 4.096 V) so the firmware can work ratiometrically
0 OHM JUMPERS (one copper layer): JP1 carries 3V3 from C2 to C8 over C8's ground link to C2 / U1; JP2 C25 -> C26's ground over VBUCK's drop into the buck; JP3 U3's ground over T_MED / SDA / SCL to its NTCs' lane; JP4 +24 V from J1.2 over J1.1's ground
TEST POINTS (copper side, 1.5 mm pads)
3.3 V: HT7533-1 (30 V max) behind R16 from the lid's 9.16 V, which drops ~1.3 V and filters spikes
PELTIERS (TES1-4902, 20 x 20 mm): both leads off the edge towards the slot, at its corners (pad 1 / pad 2, same colour on all six); thermal paste
U3 (0x49): AIN0 = PELT+ / 11, AIN1 = PELT- / 11, AIN2 = T_B, AIN3 = T_MED. U4 (0x48): AIN0 = T_EDGE, AIN1 = 3.3 V, AIN2 = T_A, AIN3 = T_TOP (string voltage = 11 x (AIN0 - AIN1) on U3: MUX 000). NTC: T = f(R), R = 10k x V / (V33 - V); PGA +-4.096 V.
PELTIER DRIVE (9.16 V from U5; its 4 x 22 uF output caps sit at VM): H-bridge straight onto the six modules in series (<= 0.67 A at full duty); I_TRIP 64/R3 = 1.25 A PWM with coast (IN1 = PWM, IN2 = 0, or the reverse), never drive / brake: firmware.md
LID BUCK (v6): +24V -> R17 1 R -> U5 TPS5430 -> L1 22 uH -> +9V (9.16 V, <= 0.75 A): the bridge and the LDO
RT1 / RT2: in the board, midway between PE2 and PE3 (strip A) and between PE4 and PE5 (strip B), facing each other across the slot: the warmest spots. RT3: at the -X edge beyond the slot end, the coldest. J2: glass-bead NTC dipping into the medium at the tip row. J3: NTC bonded to the top plate (de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
CABLE (soldered, 7 x 24-26 AWG) from the main board's lid port

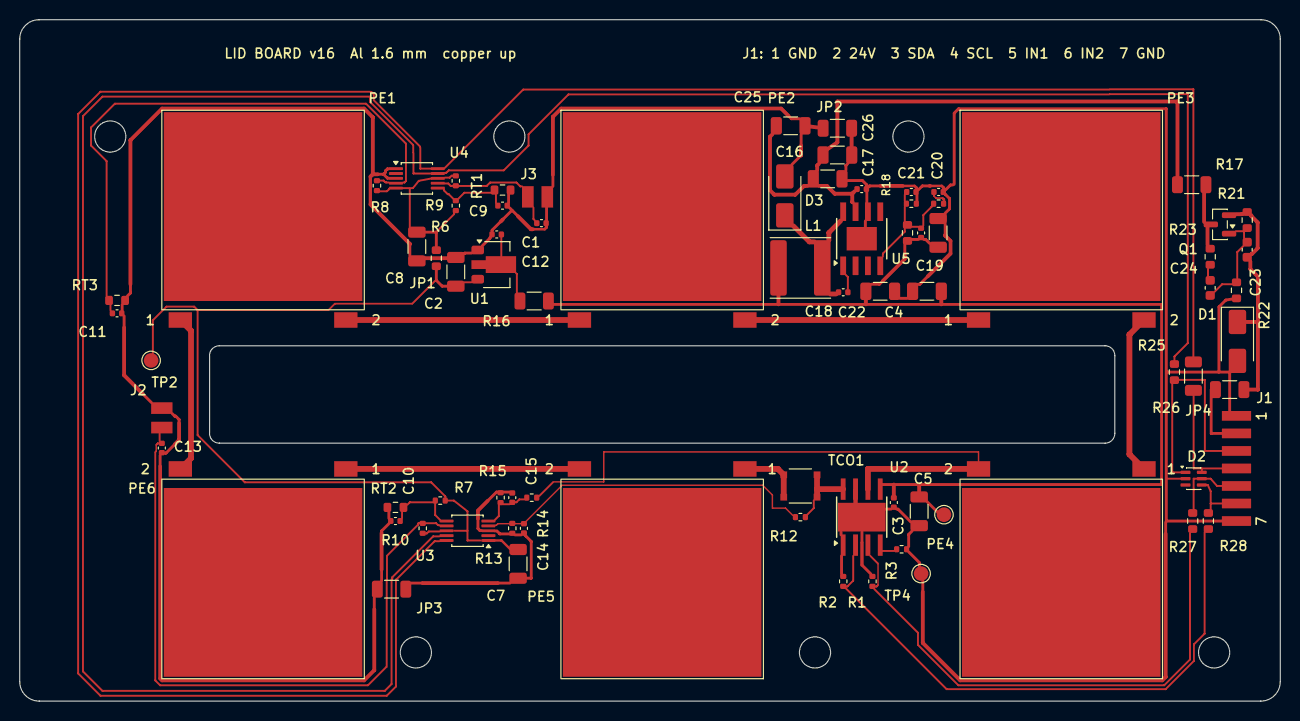
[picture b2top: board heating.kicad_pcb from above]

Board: 2 copper layers, 129.5 x 70.0 mm, 86 parts (0 on the bottom side), 37 nets.

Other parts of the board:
MH1, MH2, MH3, MH4, MH5, MH6: M3; MountingHole_3.2mm_M3

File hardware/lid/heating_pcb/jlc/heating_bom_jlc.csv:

Comment,Designator,Footprint,LCSC Part #
1u 25V,C1,C_0402_1005Metric,C52923
10u 50V,"C2,C16,C25,C26",C_1206_3216Metric,C13585
22u 25V,"C3,C4,C6,C22",C_1206_3216Metric,C12891
100n 50V,"C5,C17,C20",C_0402_1005Metric,C307331
100n 50V,"C7,C8",C_1206_3216Metric,C24497
100n,"C9,C10,C11,C12,C13,C14,C15",C_0402_1005Metric,C1525
10n 50V,C18,C_0402_1005Metric,C15195
1n 50V,C19,C_0402_1005Metric,C1523
100p 50V,C21,C_0402_1005Metric,C1546
1u 50V,C23,C_0603_1608Metric,C15849
10n 50V,C24,C_0603_1608Metric,C57112
SMAJ24A,D1,D_SMA,C19077541
SMF05CT1G,D2,SOT-363_SC-70-6,C15879
SS34,D3,D_SMA,C8678
0,JP1,R_0603_1608Metric_Jumper,C21189
0,"JP2,JP3,JP4",R_1206_3216Metric_Jumper,C17888
22u 1.4A,L1,L_Sunlord_SWPA6028S,C51349
HL2309,Q1,SOT-23,C28646263
100k,"R1,R2,R12,R14",R_0402_1005Metric,C25741
51k,R3,R_0402_1005Metric,C25794
10k,"R6,R7,R8,R9,R10,R13,R15",R_0402_1005Metric,C25744
1k,R16,R_1206_3216Metric,C4410
1,R17,R_1206_3216Metric,C17928
13k,R18,R_0603_1608Metric,C22797
2k,R19,R_0402_1005Metric,C4109
470,R20,R_0402_1005Metric,C25117
100k,R21,R_0603_1608Metric,C25803
150k,R22,R_0603_1608Metric,C22807
1k,R23,R_0603_1608Metric,C21190
100,"R25,R27,R28",R_0603_1608Metric,C22775
100,R26,R_1206_3216Metric,C17901
10k B3435 1%,"RT1,RT2,RT3",R_0603_1608Metric,C13564
SC72AAB,TCO1,Bourns_SC_TCO,C2859510
HT7533-1,U1,SOT-89-3,C14289
DRV8871DDA,U2,Texas_HTSOP-8-1EP_3.9x4.9mm_P1.27mm_EP2.95x4.9mm_NoVias,C75864
ADS1115,"U3,U4",TSSOP-10_3x3mm_P0.5mm,C37593
TPS5430DDA,U5,TI_SO-PowerPAD-8,C9864
